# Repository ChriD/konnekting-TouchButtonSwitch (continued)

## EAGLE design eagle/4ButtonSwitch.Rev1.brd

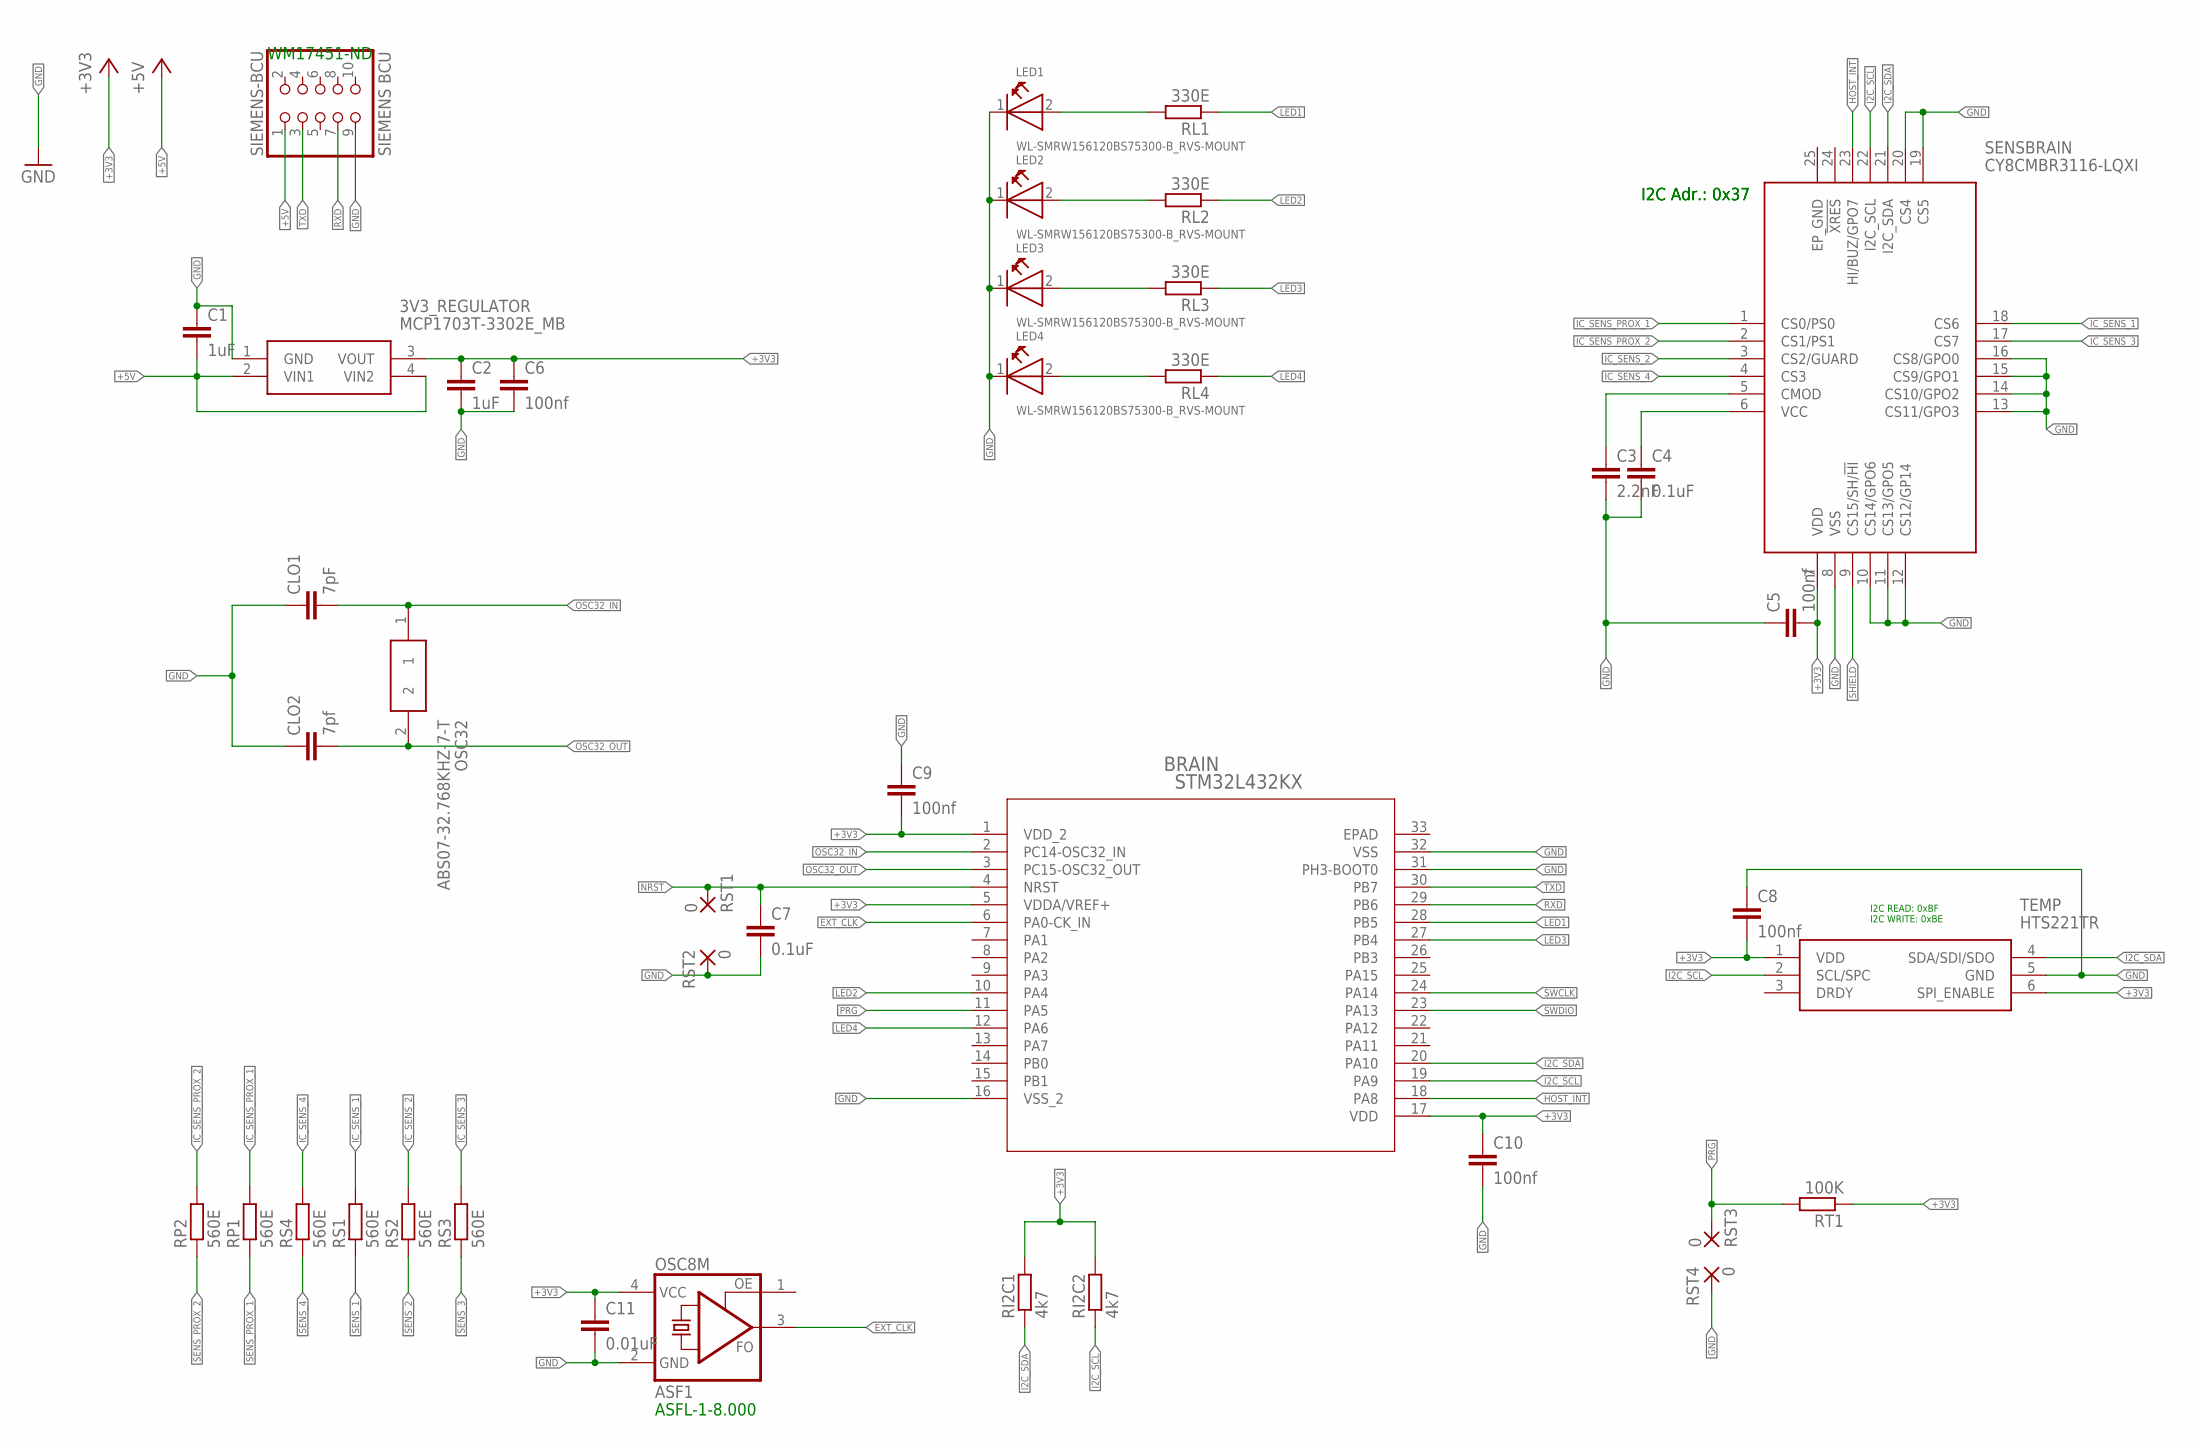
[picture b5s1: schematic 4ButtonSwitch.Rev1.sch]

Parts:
3V3_REGULATOR: MCP1703T-3302E_MB; SOT-89(MB)
BRAIN: STM32L432KX; UFQFPN32-5X5MM
C1, C2: 1uF; C0402
C3: 2.2nF; C0402
C4, C7: 0.1uF; C0402
C5, C6, C8, C9, C10: 100nf; C0402
C11: 0.01uF; C0402
CLO1: 7pF; C0402
CLO2: 7pf; C0402
LED1, LED2, LED3, LED4: WL-SMRW156120BS75300-B_RVS-MOUNT; WL-SMRW-1206-CYLDR-REVERSE-MOUNT
OSC8M: ASF1; ASF
OSC32: ABS07-32.768KHZ-7-T; ABS-07
RI2C1, RI2C2: 4k7; R0402
RL1, RL2, RL3, RL4: 330E; R0402
RP1, RP2: 560E; R0402
RS1, RS2, RS3, RS4: 560E; R0402
RST1, RST2, RST3, RST4: 0; SMD2,54-5,08
RT1: 100K; R0402
SENSBRAIN: CY8CMBR3116-LQXI; QFN50P400X400X60-25N
SIEMENS-BCU: SIEMENS BCU; 2X05SMD
TEMP: HTS221TR; HLGA-6L

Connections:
+3V3: 3V3_REGULATOR.3 (VOUT), BRAIN.1 (VDD_2), BRAIN.5 (VDDA/VREF+), BRAIN.17 (VDD), C2.1, C5.2, C6.1, C8.2, C9.2, C10.1, C11.1, OSC8M.4 (VCC), RI2C1.2, RI2C2.2, RT1.1, SENSBRAIN.7 (VDD), TEMP.1 (VDD), TEMP.6 (SPI_ENABLE)
+5V: 3V3_REGULATOR.2 (VIN1), 3V3_REGULATOR.4 (VIN2), C1.2, SIEMENS-BCU.1
CMOD: C3.1, SENSBRAIN.5 (CMOD)
EP_GND: SENSBRAIN.25 (EP_GND)
EXT_CLK: BRAIN.6 (PA0-CK_IN), OSC8M.3 (FO)
GND: 3V3_REGULATOR.1 (GND), BRAIN.16 (VSS_2), BRAIN.31 (PH3-BOOT0), BRAIN.32 (VSS), C1.1, C2.2, C3.2, C4.2, C5.1, C6.2, C7.2, C8.1, C9.1, C10.2, C11.2, CLO1.1, CLO2.1, LED1.1 (K), LED2.1 (K), LED3.1 (K), LED4.1 (K), OSC8M.2 (GND), RST2.1, RST4.1, SENSBRAIN.8 (VSS), SENSBRAIN.10 (CS14/GPO6), SENSBRAIN.11 (CS13/GPO5), SENSBRAIN.12 (CS12/GP14), SENSBRAIN.13 (CS11/GPO3), SENSBRAIN.14 (CS10/GPO2), SENSBRAIN.15 (CS9/GPO1), SENSBRAIN.16 (CS8/GPO0), SENSBRAIN.19 (CS5), SENSBRAIN.20 (CS4), SIEMENS-BCU.9, TEMP.5 (GND)
HOST_INT: BRAIN.18 (PA8), SENSBRAIN.23 (HI/BUZ/GPO7)
I2C_SCL: BRAIN.19 (PA9), RI2C2.1, SENSBRAIN.22 (I2C_SCL), TEMP.2 (SCL/SPC)
I2C_SDA: BRAIN.20 (PA10), RI2C1.1, SENSBRAIN.21 (I2C_SDA), TEMP.4 (SDA/SDI/SDO)
IC_SENS_1: RS1.2, SENSBRAIN.18 (CS6)
IC_SENS_2: RS2.2, SENSBRAIN.3 (CS2/GUARD)
IC_SENS_3: RS3.2, SENSBRAIN.17 (CS7)
IC_SENS_4: RS4.2, SENSBRAIN.4 (CS3)
IC_SENS_PROX_1: RP1.2, SENSBRAIN.1 (CS0/PS0)
IC_SENS_PROX_2: RP2.2, SENSBRAIN.2 (CS1/PS1)
LED1: BRAIN.28 (PB5), RL1.1
LED2: BRAIN.10 (PA4), RL2.1
LED3: BRAIN.27 (PB4), RL3.1
LED4: BRAIN.12 (PA6), RL4.1
unnamed: LED1.2 (A), RL1.2
unnamed: LED2.2 (A), RL2.2
unnamed: LED3.2 (A), RL3.2
unnamed: LED4.2 (A), RL4.2
NRST: BRAIN.4 (NRST), C7.1, RST1.1
OSC32_IN: BRAIN.2 (PC14-OSC32_IN), CLO1.2, OSC32.1
OSC32_OUT: BRAIN.3 (PC15-OSC32_OUT), CLO2.2, OSC32.2
PRG: BRAIN.11 (PA5), RST3.1, RT1.2
SENS_1: RS1.1
SENS_2: RS2.1
SENS_3: RS3.1
SENS_4: RS4.1
SENS_PROX_1: RP1.1
SENS_PROX_2: RP2.1
SHIELD: SENSBRAIN.9 (CS15/SH/!HI)
SWCLK: BRAIN.24 (PA14)
SWDIO: BRAIN.23 (PA13)
USART1_RX: BRAIN.30 (PB7), SIEMENS-BCU.3
USART1_TX: BRAIN.29 (PB6), SIEMENS-BCU.7
USART2_RX: BRAIN.9 (PA3)
USART2_TX: BRAIN.8 (PA2)
USB_DM: BRAIN.21 (PA11)
USB_DP: BRAIN.22 (PA12)
VCC: C4.1, SENSBRAIN.6 (VCC)

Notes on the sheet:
I2C READ: 0xBF I2C WRITE: 0xBE
ASFL-1-8.000
I2C Adr.: 0x37
WM17451-ND

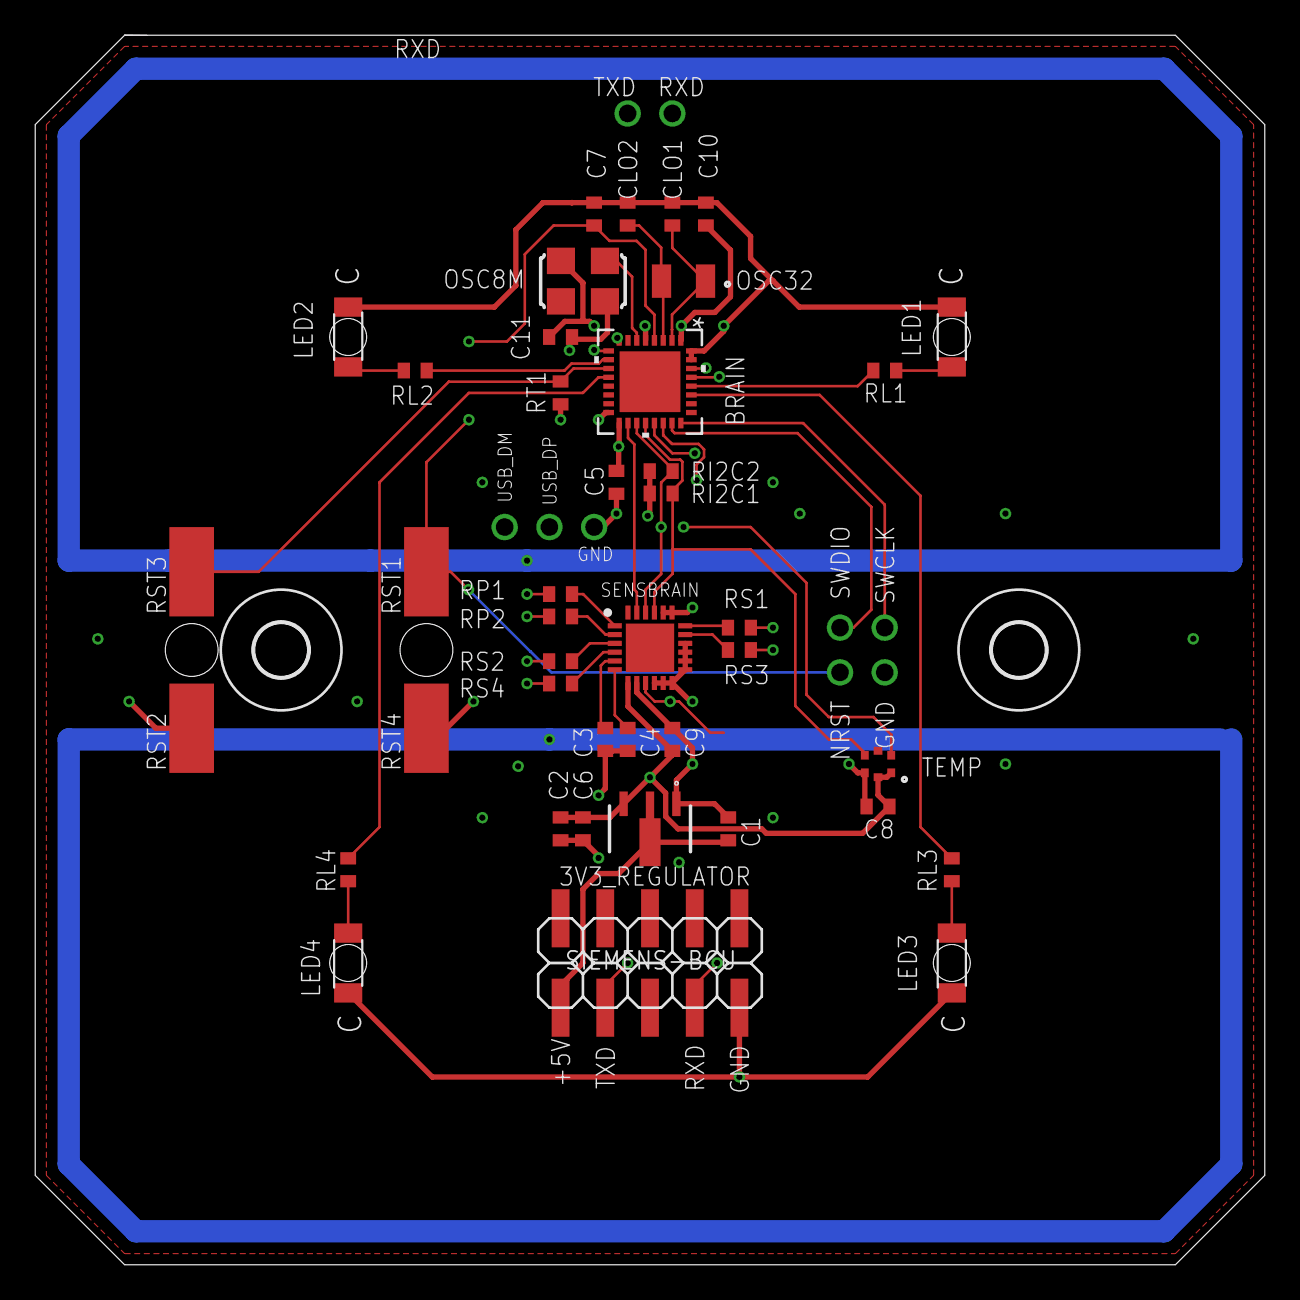
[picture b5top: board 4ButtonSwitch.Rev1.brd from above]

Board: 4 copper layers, 69.8 x 69.8 mm, 43 parts (0 on the bottom side), 29 nets.

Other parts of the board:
U$1, U$2: 3,0

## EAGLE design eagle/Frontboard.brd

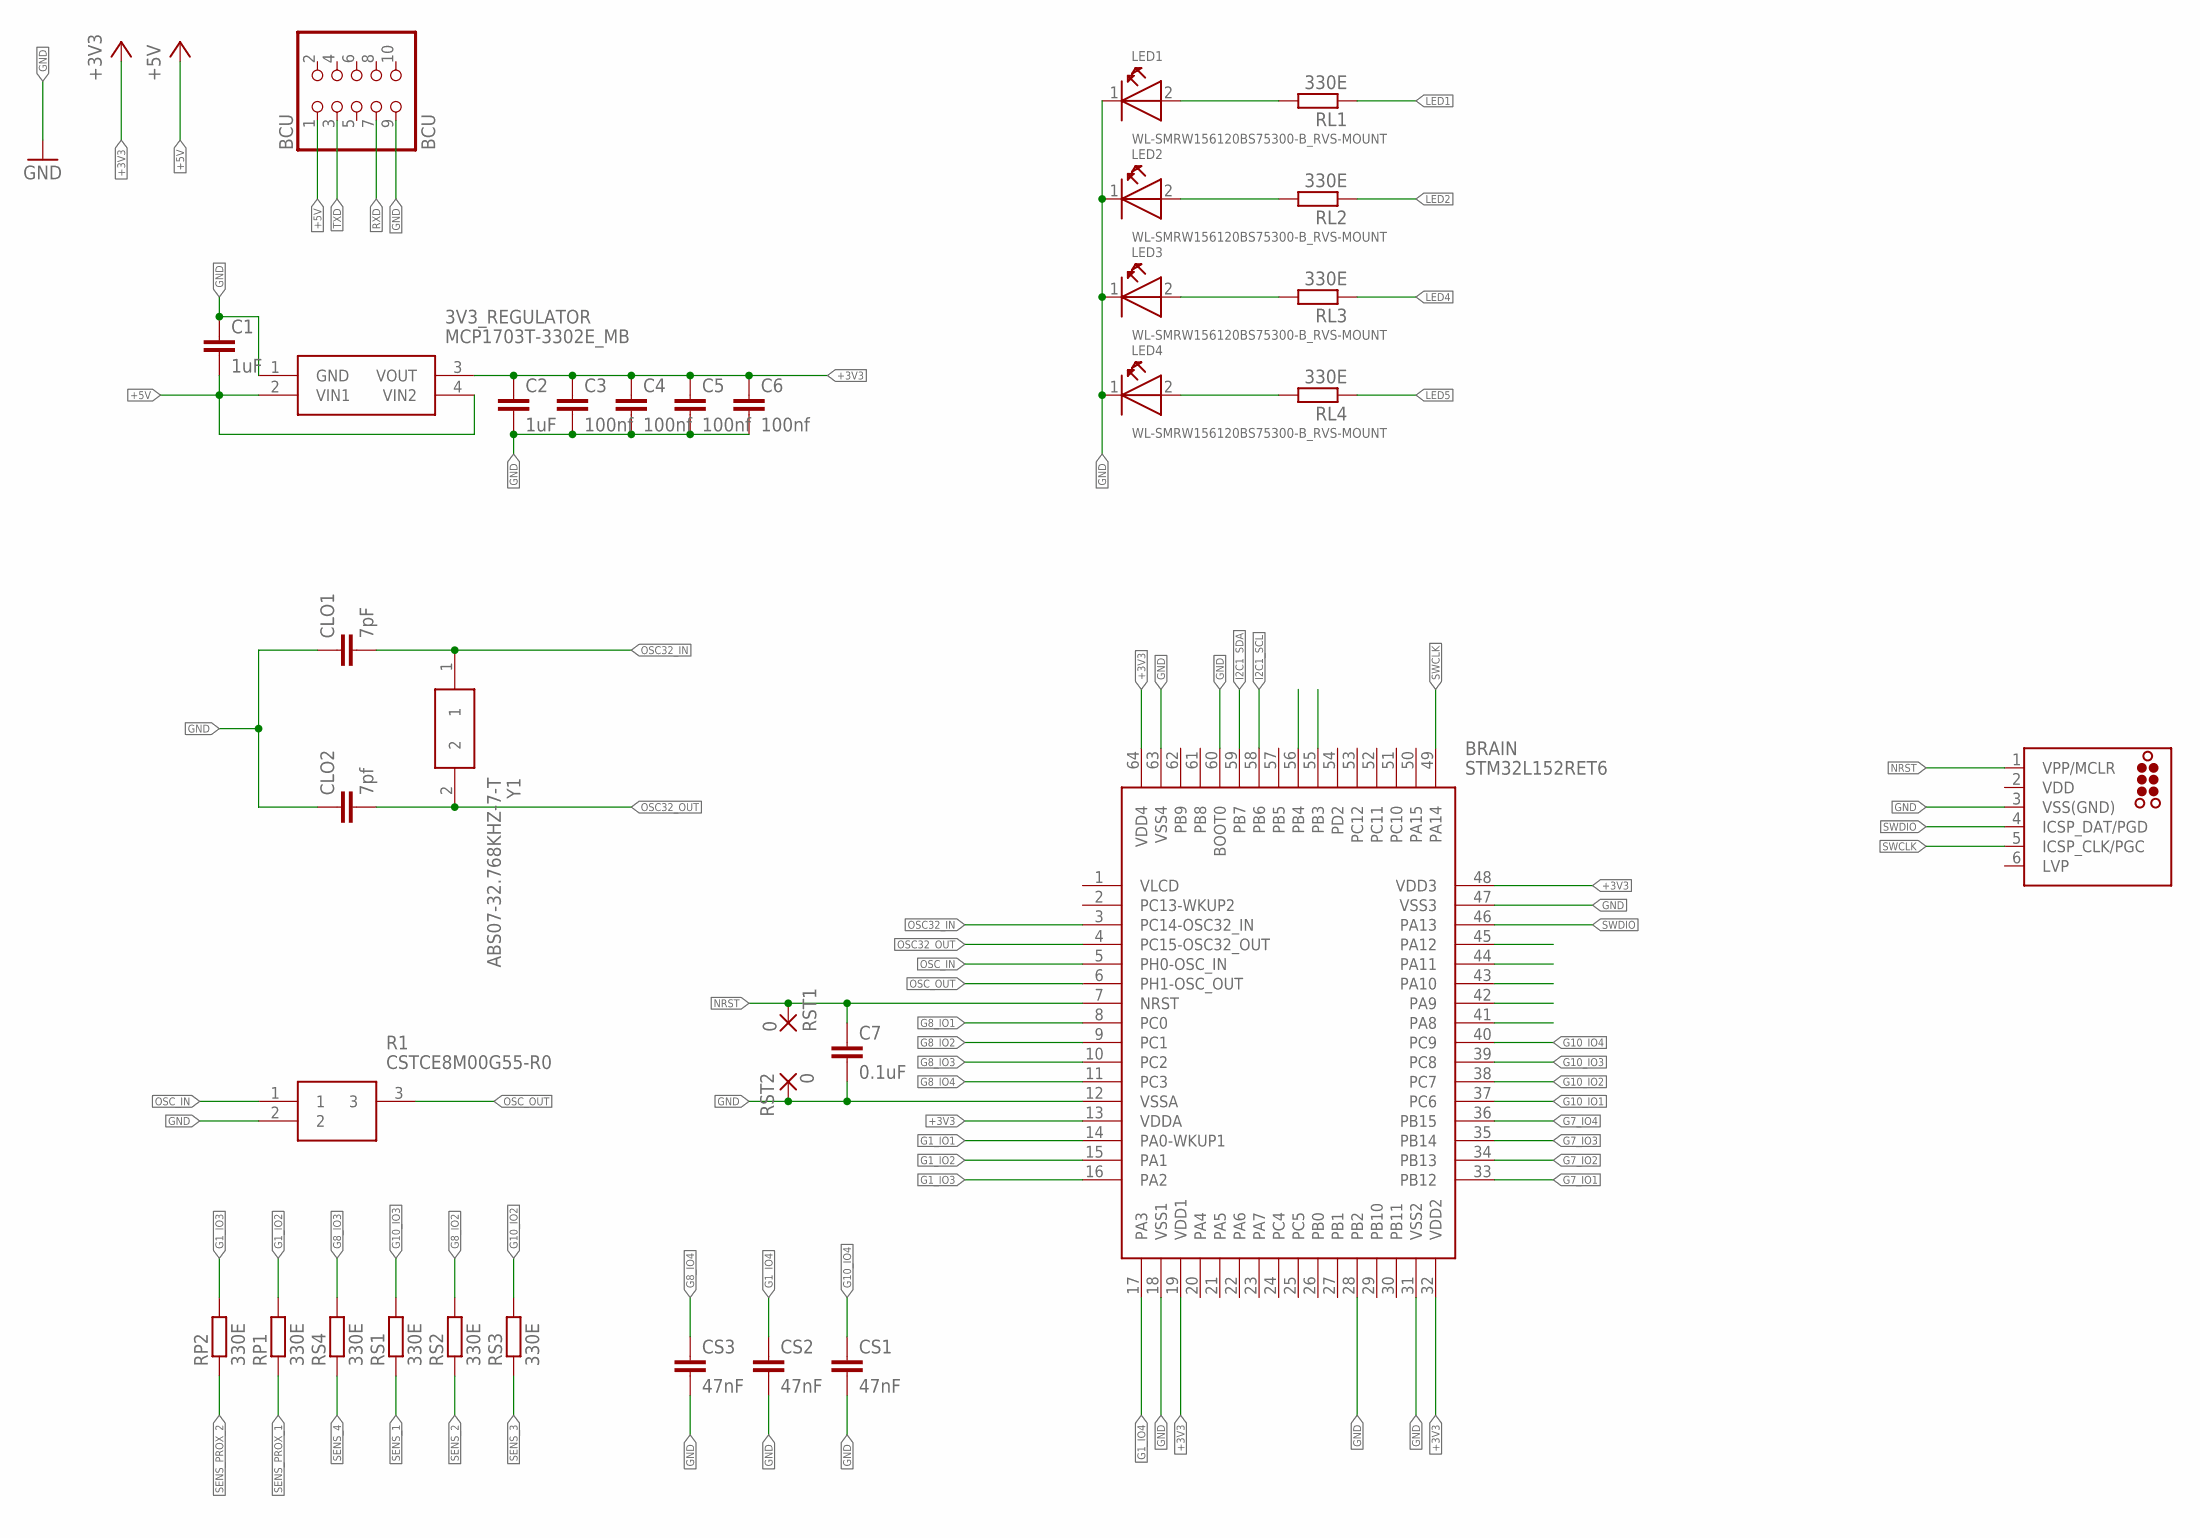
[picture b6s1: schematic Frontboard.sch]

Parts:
3V3_REGULATOR: MCP1703T-3302E_MB; SOT-89(MB)
BCU: BCU; 2X05SMD
BRAIN: STM32L152RET6; QFP50P1200X1200X160-64N
C1, C2: 1uF; C0603
C3, C4, C5, C6: 100nf; C0603
C7: 0.1uF; C0603
CLO1: 7pF; C0603
CLO2: 7pf; C0603
CS1, CS2, CS3: 47nF; C0603
LED1, LED2, LED3, LED4: WL-SMRW156120BS75300-B_RVS-MOUNT; WL-SMRW-1206-CYLDR-REVERSE-MOUNT
R1: CSTCE8M00G55-R0; CSTCE12M0G55-R0
RL1, RL2, RL3, RL4: 330E; R0603
RP1, RP2: 330E; R0603
RS1, RS2, RS3, RS4: 330E; R0603
RST1, RST2: 0; SMD2,54-5,08
SWD: SWD; TC2030-MCP-NL
Y1: ABS07-32.768KHZ-7-T; ABS-07

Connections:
+3V3: 3V3_REGULATOR.3 (VOUT), BRAIN.13 (VDDA), BRAIN.19 (VDD1), BRAIN.32 (VDD2), BRAIN.48 (VDD3), BRAIN.64 (VDD4), C2.1, C3.1, C4.1, C5.1, C6.1; also elsewhere on the board
+5V: 3V3_REGULATOR.2 (VIN1), 3V3_REGULATOR.4 (VIN2), BCU.1, C1.2
G1_IO1: BRAIN.14 (PA0-WKUP1)
G1_IO2: BRAIN.15 (PA1), RP1.2
G1_IO3: BRAIN.16 (PA2), RP2.2
G1_IO4: BRAIN.17 (PA3), CS2.1
G7_IO2: BRAIN.34 (PB13)
G7_IO3: BRAIN.35 (PB14)
G7_IO4: BRAIN.36 (PB15)
G8_IO1: BRAIN.8 (PC0)
G8_IO2: BRAIN.9 (PC1), RS2.2
G8_IO3: BRAIN.10 (PC2), RS4.2
G8_IO4: BRAIN.11 (PC3), CS3.1
G10_IO1: BRAIN.37 (PC6)
G10_IO2: BRAIN.38 (PC7), RS3.2
G10_IO3: BRAIN.39 (PC8), RS1.2
G10_IO4: BRAIN.40 (PC9), CS1.1
GND: 3V3_REGULATOR.1 (GND), BCU.9, BRAIN.12 (VSSA), BRAIN.18 (VSS1), BRAIN.28 (PB2), BRAIN.31 (VSS2), BRAIN.47 (VSS3), BRAIN.60 (BOOT0), BRAIN.63 (VSS4), C1.1, C2.2, C3.2, C4.2, C5.2, C6.2, C7.2, CLO1.1, CLO2.1, CS1.2, CS2.2, CS3.2, LED1.1 (K), LED2.1 (K), LED3.1 (K), LED4.1 (K), R1.2, RST2.1, SWD.3 (VSS(GND)); also elsewhere on the board
I2C1_SCL: BRAIN.58 (PB6)
I2C1_SDA: BRAIN.59 (PB7)
I2C2_SCL: BRAIN.29 (PB10); also elsewhere on the board
I2C2_SDA: BRAIN.30 (PB11); also elsewhere on the board
LED1: BRAIN.51 (PC10), RL1.1
LED2: BRAIN.2 (PC13-WKUP2), RL2.1
LED4: BRAIN.27 (PB1), RL4.1
unnamed: LED1.2 (A), RL1.2
unnamed: LED2.2 (A), RL2.2
unnamed: LED3.2 (A), RL3.2
unnamed: LED4.2 (A), RL4.2
NRST: BRAIN.7 (NRST), C7.1, RST1.1, SWD.1 (VPP/MCLR)
OSC32_IN: BRAIN.3 (PC14-OSC32_IN), CLO1.2, Y1.1
OSC32_OUT: BRAIN.4 (PC15-OSC32_OUT), CLO2.2, Y1.2
OSC_IN: BRAIN.5 (PH0-OSC_IN), R1.1
OSC_OUT: BRAIN.6 (PH1-OSC_OUT), R1.3
PRG: BRAIN.45 (PA12); also elsewhere on the board
RXD: BCU.7
SENS_1: RS1.1
SENS_2: RS2.1
SENS_3: RS3.1
SENS_4: RS4.1
SENS_PROX_1: RP1.1
SENS_PROX_2: RP2.1
SWCLK: BRAIN.49 (PA14), SWD.5 (ICSP_CLK/PGC)
SWDIO: BRAIN.46 (PA13), SWD.4 (ICSP_DAT/PGD)
TXD: BCU.3
VDD: SWD.2 (VDD)
VLCD: BRAIN.1 (VLCD)

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
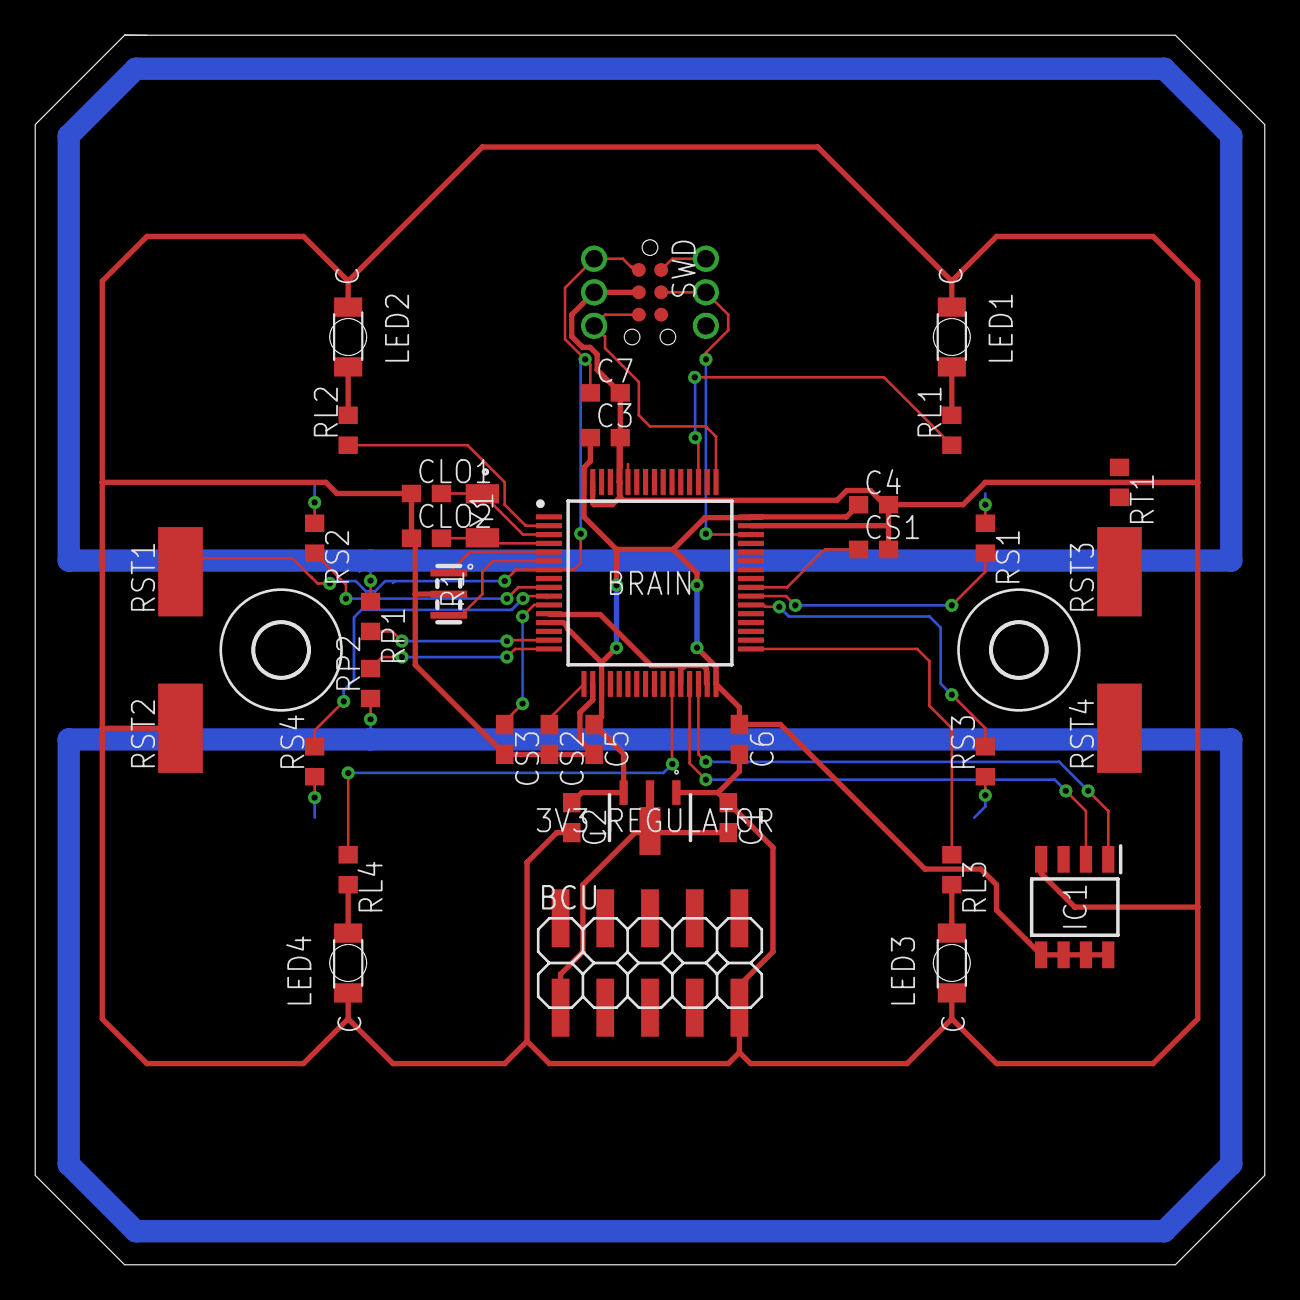
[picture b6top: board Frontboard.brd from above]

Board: 2 copper layers, 69.8 x 69.8 mm, 40 parts (0 on the bottom side), 30 nets.

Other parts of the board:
IC1: NCT75DR2G; SOIC127P600X175-8N
RST3, RST4: 0; SMD2,54-5,08
RT1: 100K; R0603
U$1, U$2: 3,0

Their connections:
+3V3: IC1.5, IC1.6, IC1.7, IC1.8, RT1.1; also elsewhere on the board
GND: IC1.4, RST4.1; also elsewhere on the board
I2C2_SCL: IC1.2; also elsewhere on the board
I2C2_SDA: IC1.1; also elsewhere on the board
PRG: RST3.1, RT1.2; also elsewhere on the board

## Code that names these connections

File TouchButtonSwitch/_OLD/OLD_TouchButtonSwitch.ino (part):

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#define SENSORID_4        4

// define the led pins for the given buttons
#define SENSORLED_1_PIN        PA11
#define SENSORLED_2_PIN        PB9
#define SENSORLED_3_PIN        PA10
#define SENSORLED_4_PIN        PA4

// This is the time in miliseconds how long the button should wait after setup to allow touch_threshold
// There has to be a enough time for the user to put the frontplate on the switch before recalibration of
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//#define NOBCU


HardwareSerial SerialDBG(PA3, PA2);
HardwareSerial SerialBCU(PC5, PC4);
#define DEBUGSERIAL       SerialDBG
#define KNX_SERIAL        SerialBCU
#define PROG_LED_PIN      0
#define PROG_BUTTON_PIN   PB1
#define TC_INTERRUPTPIN   PC0

// the differnt type of switches we do have
// currently we do have only a 4x switch type
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  delay(150);

  // startup I2C
  Wire.setSCL(PA8);
  Wire.setSDA(PC9);
  Wire.begin();

  touchSwitch->changeMode(TS_MODE_STARTUP2, true);
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
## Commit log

2018-05-16 Initial
2018-05-16 test commit
2018-06-08 1.0.0
2018-07-06 Rev 2
2018-07-09 Rev 2.1
2018-07-10 Rev2.1
2018-08-30 update for cost efficient board manufacturing
2019-01-16 upload
2020-02-12 minor updates
